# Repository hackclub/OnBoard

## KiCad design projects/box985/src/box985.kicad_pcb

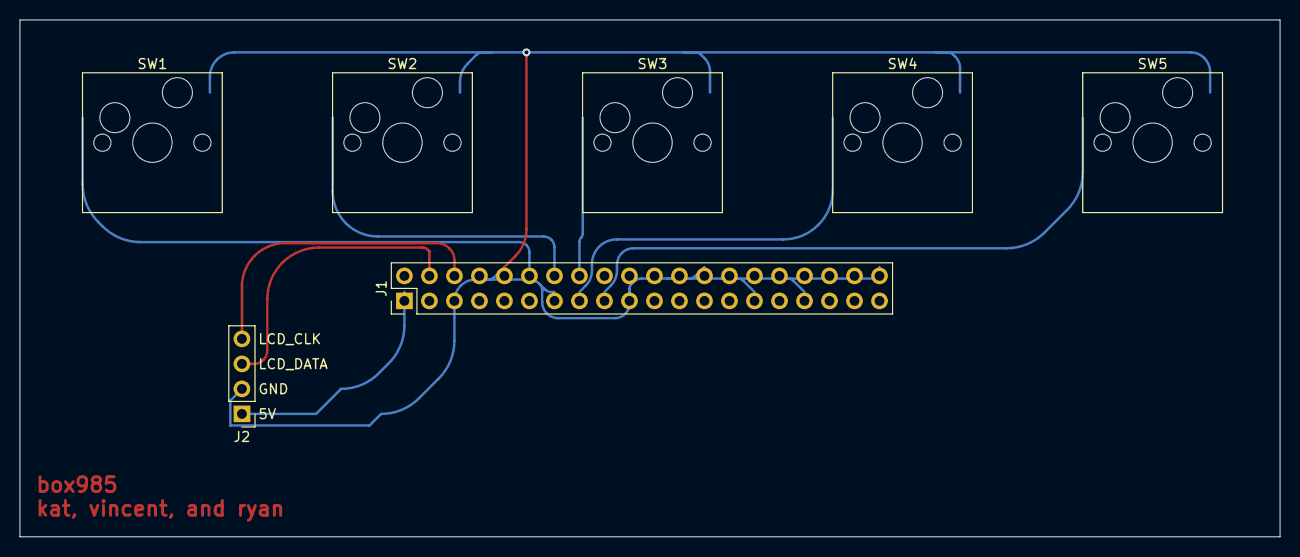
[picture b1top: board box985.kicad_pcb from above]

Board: 2 copper layers, 128.0 x 52.5 mm, 7 parts (0 on the bottom side), 9 nets.

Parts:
J1: Conn_02x20_Odd_Even; PinHeader_2x20_P2.54mm_Vertical
J2: Conn_01x04; PinHeader_1x04_P2.54mm_Vertical
SW1, SW2, SW3, SW4, SW5: Switch; Hotswap_MX

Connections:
+5V: J1.2, J2.1
GND: J1.6, J1.9, J1.14, J1.20, J1.25, J1.30, J1.34, J1.39, J2.2, SW1.2, SW2.2, SW3.2, SW4.2, SW5.2
GPIO 17: J1.11, SW1.1
GPIO 22: J1.15, SW3.1
GPIO 23: J1.16, SW4.1
GPIO 24: J1.18, SW5.1
GPIO 27: J1.13, SW2.1
LCD_CLK: J1.5, J2.4
LCD_DATA: J1.3, J2.3

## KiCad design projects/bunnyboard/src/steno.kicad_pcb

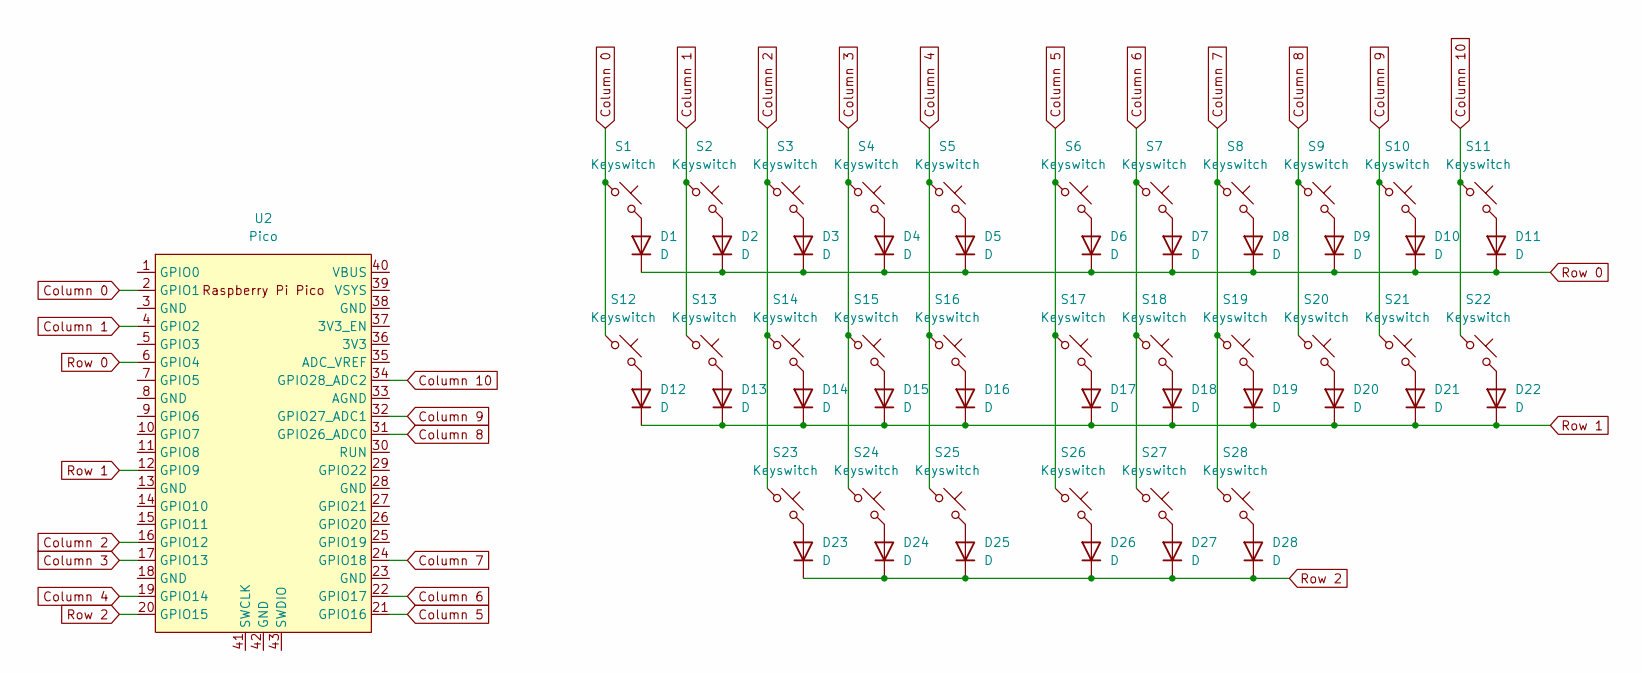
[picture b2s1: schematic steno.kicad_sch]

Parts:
D1, D2, D3, D4, D5, D6, D7, D8, D9, D10, D11, D12, D13, D14, D15, D16, D17, D18, D19, D20, D21, D22, D23, D24, D25, D26, D27, D28: D; Diode_DO-35
S1, S2, S3, S4, S5, S6, S7, S8, S9, S10, S11, S12, S13, S14, S15, S16, S17, S18, S19, S20, S21, S22, S23, S24, S25, S26, S27, S28: Keyswitch; Choc_V1_1.00u
U2: Pico; RPi_PicoW_SMD_TH

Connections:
Column 0: S1.1, S12.1, U2.2 (GPIO1)
Column 1: S2.1, S13.1, U2.4 (GPIO2)
Column 2: S3.1, S14.1, S23.1, U2.16 (GPIO12)
Column 3: S4.1, S15.1, S24.1, U2.17 (GPIO13)
Column 4: S5.1, S16.1, S25.1, U2.19 (GPIO14)
Column 5: S6.1, S17.1, S26.1, U2.21 (GPIO16)
Column 6: S7.1, S18.1, S27.1, U2.22 (GPIO17)
Column 7: S8.1, S19.1, S28.1, U2.24 (GPIO18)
Column 8: S9.1, S20.1, U2.31 (GPIO26_ADC0)
Column 9: S10.1, S21.1, U2.32 (GPIO27_ADC1)
Column 10: S11.1, S22.1, U2.34 (GPIO28_ADC2)
unnamed: D1.2 (A), S1.2
unnamed: D2.2 (A), S2.2
unnamed: D3.2 (A), S3.2
unnamed: D4.2 (A), S4.2
unnamed: D5.2 (A), S5.2
unnamed: D6.2 (A), S6.2
unnamed: D7.2 (A), S7.2
unnamed: D8.2 (A), S8.2
unnamed: D9.2 (A), S9.2
unnamed: D10.2 (A), S10.2
unnamed: D11.2 (A), S11.2
unnamed: D12.2 (A), S12.2
unnamed: D13.2 (A), S13.2
unnamed: D14.2 (A), S14.2
unnamed: D15.2 (A), S15.2
unnamed: D16.2 (A), S16.2
unnamed: D17.2 (A), S17.2
unnamed: D18.2 (A), S18.2
unnamed: D19.2 (A), S19.2
unnamed: D20.2 (A), S20.2
unnamed: D21.2 (A), S21.2
unnamed: D22.2 (A), S22.2
unnamed: D23.2 (A), S23.2
unnamed: D24.2 (A), S24.2
unnamed: D25.2 (A), S25.2
unnamed: D26.2 (A), S26.2
unnamed: D27.2 (A), S27.2
unnamed: D28.2 (A), S28.2
Row 0: D1.1 (K), D2.1 (K), D3.1 (K), D4.1 (K), D5.1 (K), D6.1 (K), D7.1 (K), D8.1 (K), D9.1 (K), D10.1 (K), D11.1 (K), U2.6 (GPIO4)
Row 1: D12.1 (K), D13.1 (K), D14.1 (K), D15.1 (K), D16.1 (K), D17.1 (K), D18.1 (K), D19.1 (K), D20.1 (K), D21.1 (K), D22.1 (K), U2.12 (GPIO9)
Row 2: D23.1 (K), D24.1 (K), D25.1 (K), D26.1 (K), D27.1 (K), D28.1 (K), U2.20 (GPIO15)

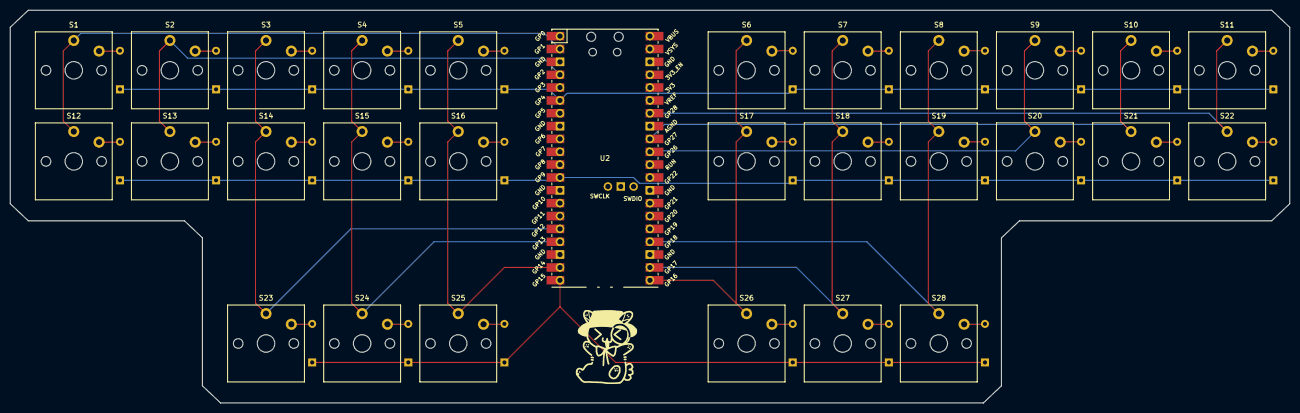
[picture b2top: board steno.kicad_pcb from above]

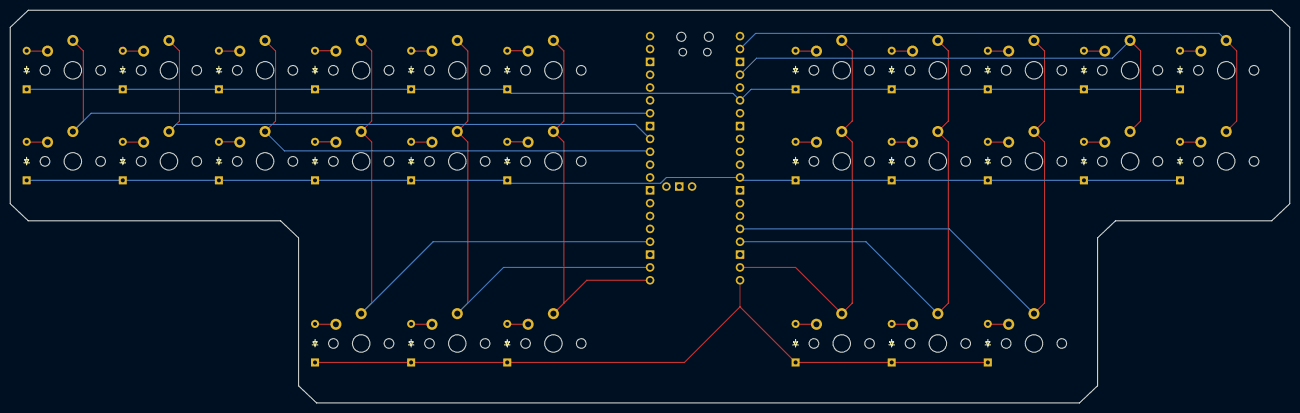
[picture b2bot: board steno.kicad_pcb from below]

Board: 2 copper layers, 252.9 x 77.6 mm, 57 parts (28 on the bottom side), 42 nets.

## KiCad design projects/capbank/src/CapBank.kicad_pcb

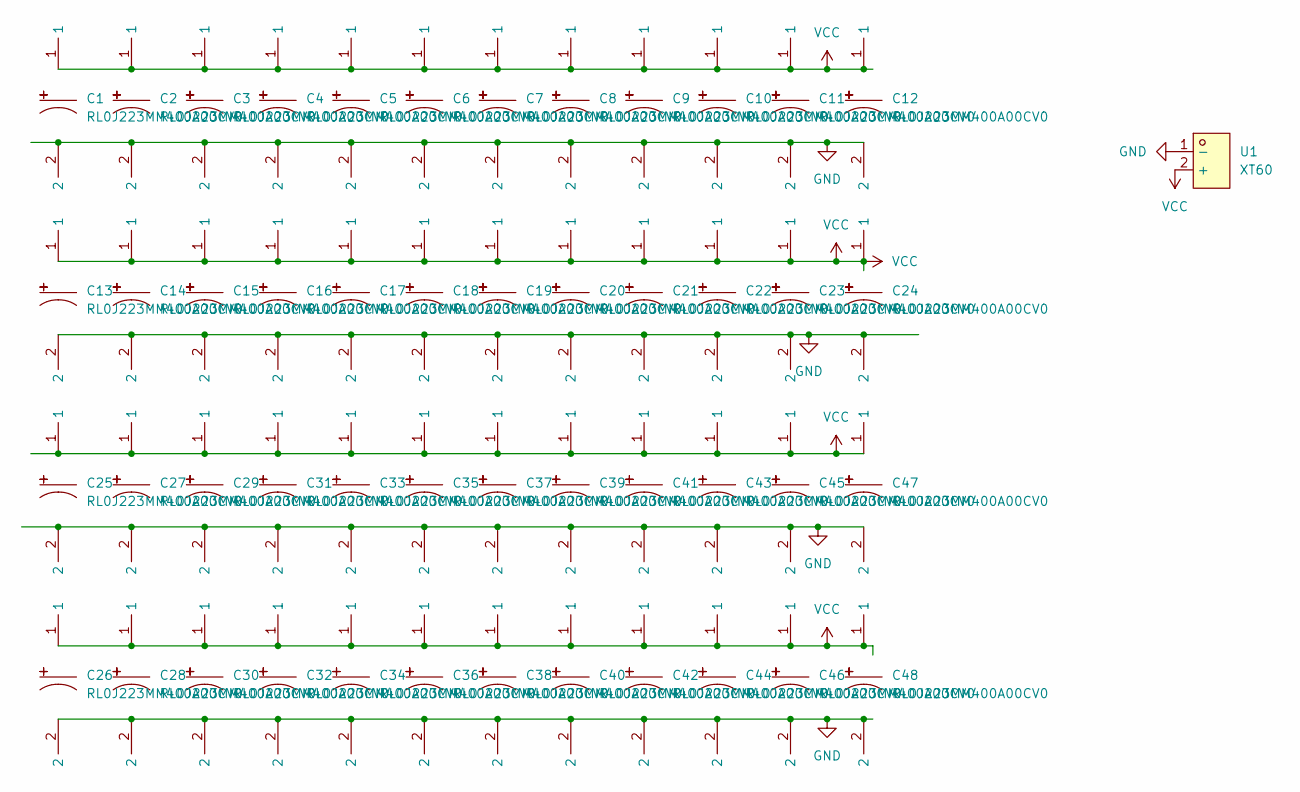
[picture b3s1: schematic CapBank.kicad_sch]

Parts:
C1, C2, C3, C4, C5, C6, C7, C8, C9, C10, C11, C12, C13, C14, C15, C16, C17, C18, C19, C20, C21, C22, C23, C24, C25, C26, C27, C28, C29, C30, C31, C32, C33, C34, C35, C36, C37, C38, C39, C40, C41, C42, C43, C44, C45, C46, C47, C48: RL0J223MM400A00CV0; CAP-TH_BD18.0-P7.50-D1.2-FD; LCSC Part C315548
U1: XT60; CONN-TH_XT60; LCSC Part C98733

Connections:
GND: C1.2, C2.2, C3.2, C4.2, C5.2, C6.2, C7.2, C8.2, C9.2, C10.2, C11.2, C12.2, C13.2, C14.2, C15.2, C16.2, C17.2, C18.2, C19.2, C20.2, C21.2, C22.2, C23.2, C24.2, C25.2, C26.2, C27.2, C28.2, C29.2, C30.2, C31.2, C32.2, C33.2, C34.2, C35.2, C36.2, C37.2, C38.2, C39.2, C40.2, C41.2, C42.2, C43.2, C44.2, C45.2, C46.2, C47.2, C48.2, U1.1 (-)
VCC: C1.1, C2.1, C3.1, C4.1, C5.1, C6.1, C7.1, C8.1, C9.1, C10.1, C11.1, C12.1, C13.1, C14.1, C15.1, C16.1, C17.1, C18.1, C19.1, C20.1, C21.1, C22.1, C23.1, C24.1, C25.1, C26.1, C27.1, C28.1, C29.1, C30.1, C31.1, C32.1, C33.1, C34.1, C35.1, C36.1, C37.1, C38.1, C39.1, C40.1, C41.1, C42.1, C43.1, C44.1, C45.1, C46.1, C47.1, C48.1, U1.2 (+)

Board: 2 copper layers, 49 parts (0 on the bottom side), 2 nets, no tracks yet.

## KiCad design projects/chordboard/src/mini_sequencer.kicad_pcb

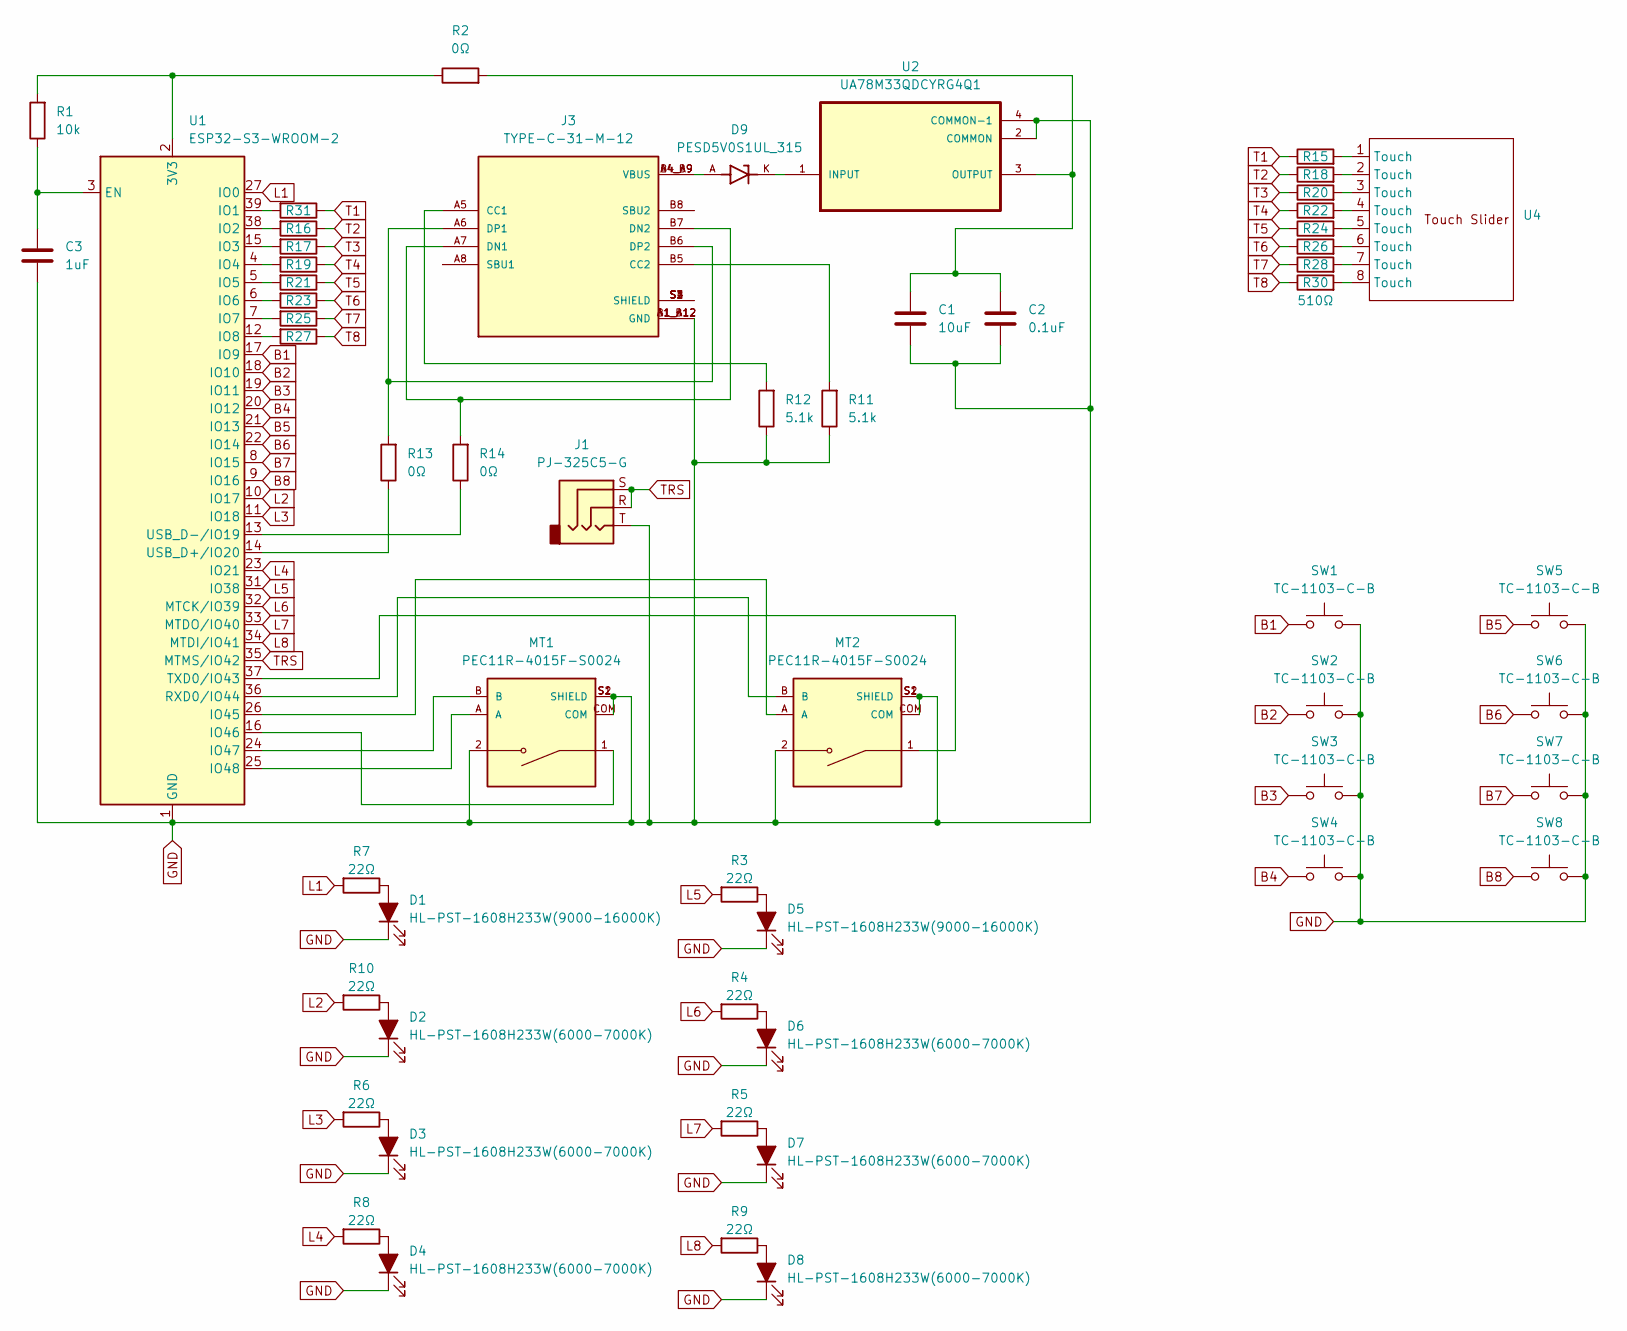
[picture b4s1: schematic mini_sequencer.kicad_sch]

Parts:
C1: 10uF; C1608X5R1E106M080AC_CAPC1608X100N; LCSC C2909630
C2: 0.1uF; CGA3E2X7R1H104K080AA_CAPC1608X90N; LCSC C149620
C3: 1uF; EMK107B7105KA-T_CAPC1608X90N; LCSC C385893
D1, D5: HL-PST-1608H233W(9000-16000K); LED_0603_1608Metric; LCSC C219226
D2, D3, D4, D6, D7, D8: HL-PST-1608H233W(6000-7000K); LED_0603_1608Metric; LCSC C219227
D9: PESD5V0S1UL_315; PESD5V0S1UL_315_DIO_PESD5V0S1UL_315; LCSC C85402
J1: PJ-325C5-G; Jack_3.5mm_CUI_SJ1-3535NG_Horizontal; LCSC C692438
J3: TYPE-C-31-M-12; TYPE-C-31-M-12_HRO_TYPE-C-31-M-12; PARTREV 2020.12.08; LCSC C165948
MT1, MT2: PEC11R-4015F-S0024; PEC11R-4215F-S0024_XDCR_PEC11R-4215F-S0024; PARTREV Rev. 09/19; LCSC C143789
R1: 10k; MCS04020C1002FE000_RESC1005X37N; LCSC C190095
R2, R13, R14, R16, R17, R19, R21, R23, R25, R27, R31: 0Ω; R_0201_0603Metric; LCSC C4085635
R3, R4, R5, R6, R7, R8, R9, R10: 22Ω; R_0201_0603Metric; LCSC C862626
R11, R12: 5.1k; R_0201_0603Metric; LCSC C122969
R15, R18, R20, R22, R28, R30: 510Ω; R_0201_0603Metric; LCSC C860427
R24, R26: 510Ω; R_0201_0603Metric
SW1, SW2, SW3, SW4, SW5, SW6, SW7, SW8: TC-1103-C-B; SW_PUSH-12mm; LCSC C840834
U1: ESP32-S3-WROOM-2; LCSC C2913202
U2: UA78M33QDCYRG4Q1; UA78M33QDCYRG4Q1_SOT230P700X180-4N; LCSC C131952
U4: TouchSlider-8_50x15mm

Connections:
B1: SW1.1, U1.17 (IO9)
B2: SW2.1, U1.18 (IO10)
B3: SW3.1, U1.19 (IO11)
B4: SW4.1, U1.20 (IO12)
B5: SW5.1, U1.21 (IO13)
B6: SW6.1, U1.22 (IO14)
B7: SW7.1, U1.8 (IO15)
B8: SW8.1, U1.9 (IO16)
GND: C1.2, C2.2, C3.1, D1.1 (K), D2.1 (K), D3.1 (K), D4.1 (K), D5.1 (K), D6.1 (K), D7.1 (K), D8.1 (K), J1.T, J3.A1_B12 (GND), J3.B1_A12 (GND), MT1.2, MT1.COM, MT1.S1 (SHIELD), MT1.S2 (SHIELD), MT2.2, MT2.COM, MT2.S1 (SHIELD), MT2.S2 (SHIELD), R11.1, R12.1, SW1.2, SW2.2, SW3.2, SW4.2, SW5.2, SW6.2, SW7.2, SW8.2, U1.1 (GND), U1.40 (GND), U1.41 (GND), U2.2 (COMMON), U2.4 (COMMON-1)
L1: R7.2, U1.27 (IO0)
L2: R10.2, U1.10 (IO17)
L3: R6.2, U1.11 (IO18)
L4: R8.2, U1.23 (IO21)
L5: R3.2, U1.31 (IO38)
L6: R4.2, U1.32 (MTCK/IO39)
L7: R5.2, U1.33 (MTDO/IO40)
L8: R9.2, U1.34 (MTDI/IO41)
unnamed: D1.2 (A), R7.1
unnamed: D2.2 (A), R10.1
unnamed: D3.2 (A), R6.1
unnamed: D4.2 (A), R8.1
unnamed: D5.2 (A), R3.1
unnamed: D6.2 (A), R4.1
unnamed: D7.2 (A), R5.1
unnamed: D8.2 (A), R9.1
unnamed: D9.A, J3.A4_B9 (VBUS), J3.B4_A9 (VBUS)
unnamed: J3.A5 (CC1), R12.2
unnamed: J3.B5 (CC2), R11.2
unnamed: J3.A7 (DN1), J3.B7 (DN2), R14.2
unnamed: J3.A6 (DP1), J3.B6 (DP2), R13.2
unnamed: J3.S1 (SHIELD), J3.S2 (SHIELD), J3.S3 (SHIELD), J3.S4 (SHIELD)
unnamed: R15.2, U4.1 (Touch)
unnamed: R18.2, U4.2 (Touch)
unnamed: R20.2, U4.3 (Touch)
unnamed: R22.2, U4.4 (Touch)
unnamed: R24.2, U4.5 (Touch)
unnamed: R26.2, U4.6 (Touch)
unnamed: R28.2, U4.7 (Touch)
unnamed: R30.2, U4.8 (Touch)
unnamed: R1.2, R2.1, U1.2 (3V3)
unnamed: C3.2, R1.1, U1.3 (EN)
unnamed: R31.2, U1.39 (IO1)
unnamed: R16.2, U1.38 (IO2)
unnamed: R17.2, U1.15 (IO3)
unnamed: R19.2, U1.4 (IO4)
unnamed: R21.2, U1.5 (IO5)
unnamed: R23.2, U1.6 (IO6)
unnamed: R25.2, U1.7 (IO7)
unnamed: R27.2, U1.12 (IO8)
unnamed: MT2.A, U1.26 (IO45)
unnamed: MT1.1, U1.16 (IO46)
unnamed: MT1.B, U1.24 (IO47)
unnamed: MT1.A, U1.25 (IO48)
unnamed: MT2.B, U1.36 (RXD0/IO44)
unnamed: MT2.1, U1.37 (TXD0/IO43)
unnamed: R13.1, U1.14 (USB_D+/IO20)
unnamed: R14.1, U1.13 (USB_D-/IO19)
unnamed: D9.K, U2.1 (INPUT)
unnamed: C1.1, C2.1, R2.2, U2.3 (OUTPUT)
T1: R15.1, R31.1
T2: R16.1, R18.1
T3: R17.1, R20.1
T4: R19.1, R22.1
T5: R21.1, R24.1
T6: R23.1, R26.1
T7: R25.1, R28.1
T8: R27.1, R30.1
TRS: J1.R, J1.S, U1.35 (MTMS/IO42)

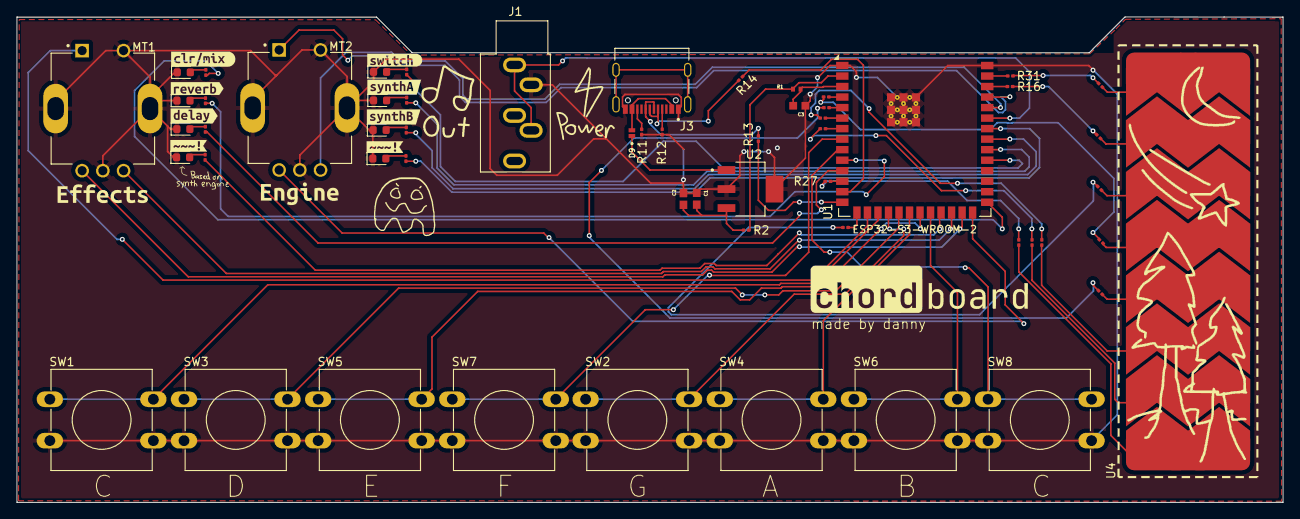
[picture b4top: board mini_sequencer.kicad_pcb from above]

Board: 2 copper layers, 152.9 x 58.6 mm, 67 parts (0 on the bottom side), 68 nets.

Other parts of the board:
kibuzzard-66F9FCB2: G***; kibuzzard-66F9FCB2
kibuzzard-66F9FCDF: G***; kibuzzard-66F9FCDF
kibuzzard-66F9FCF2: G***; kibuzzard-66F9FCF2
kibuzzard-66F9FCF7: G***; kibuzzard-66F9FCF7
kibuzzard-66F9FD07: G***; kibuzzard-66F9FD07
kibuzzard-66F9FD26: G***; kibuzzard-66F9FD26
kibuzzard-66F9FD78: G***; kibuzzard-66F9FD78
kibuzzard-66FCC2B4: G***; kibuzzard-66FCC2B4
kibuzzard-66FCC410: G***; kibuzzard-66FCC410
kibuzzard-6702CE24: G***; kibuzzard-6702CE24

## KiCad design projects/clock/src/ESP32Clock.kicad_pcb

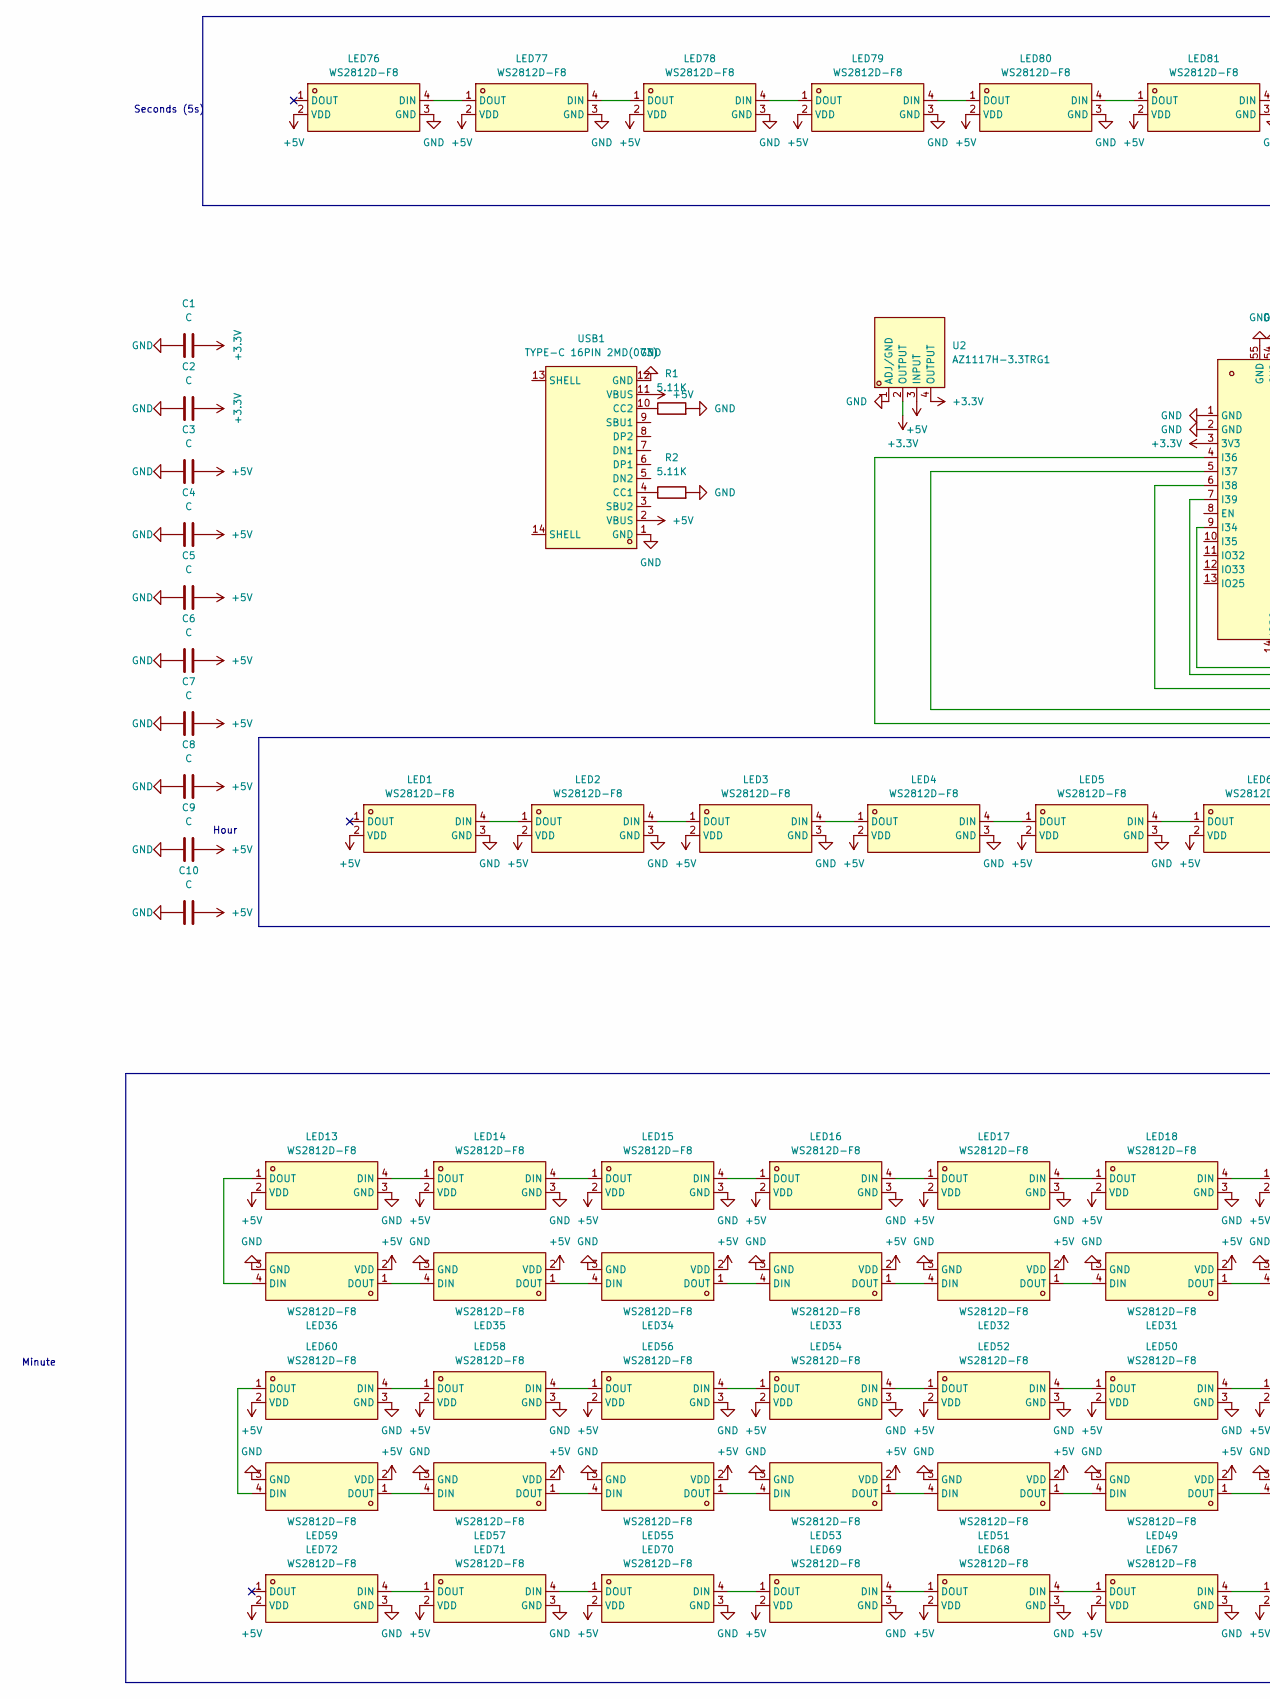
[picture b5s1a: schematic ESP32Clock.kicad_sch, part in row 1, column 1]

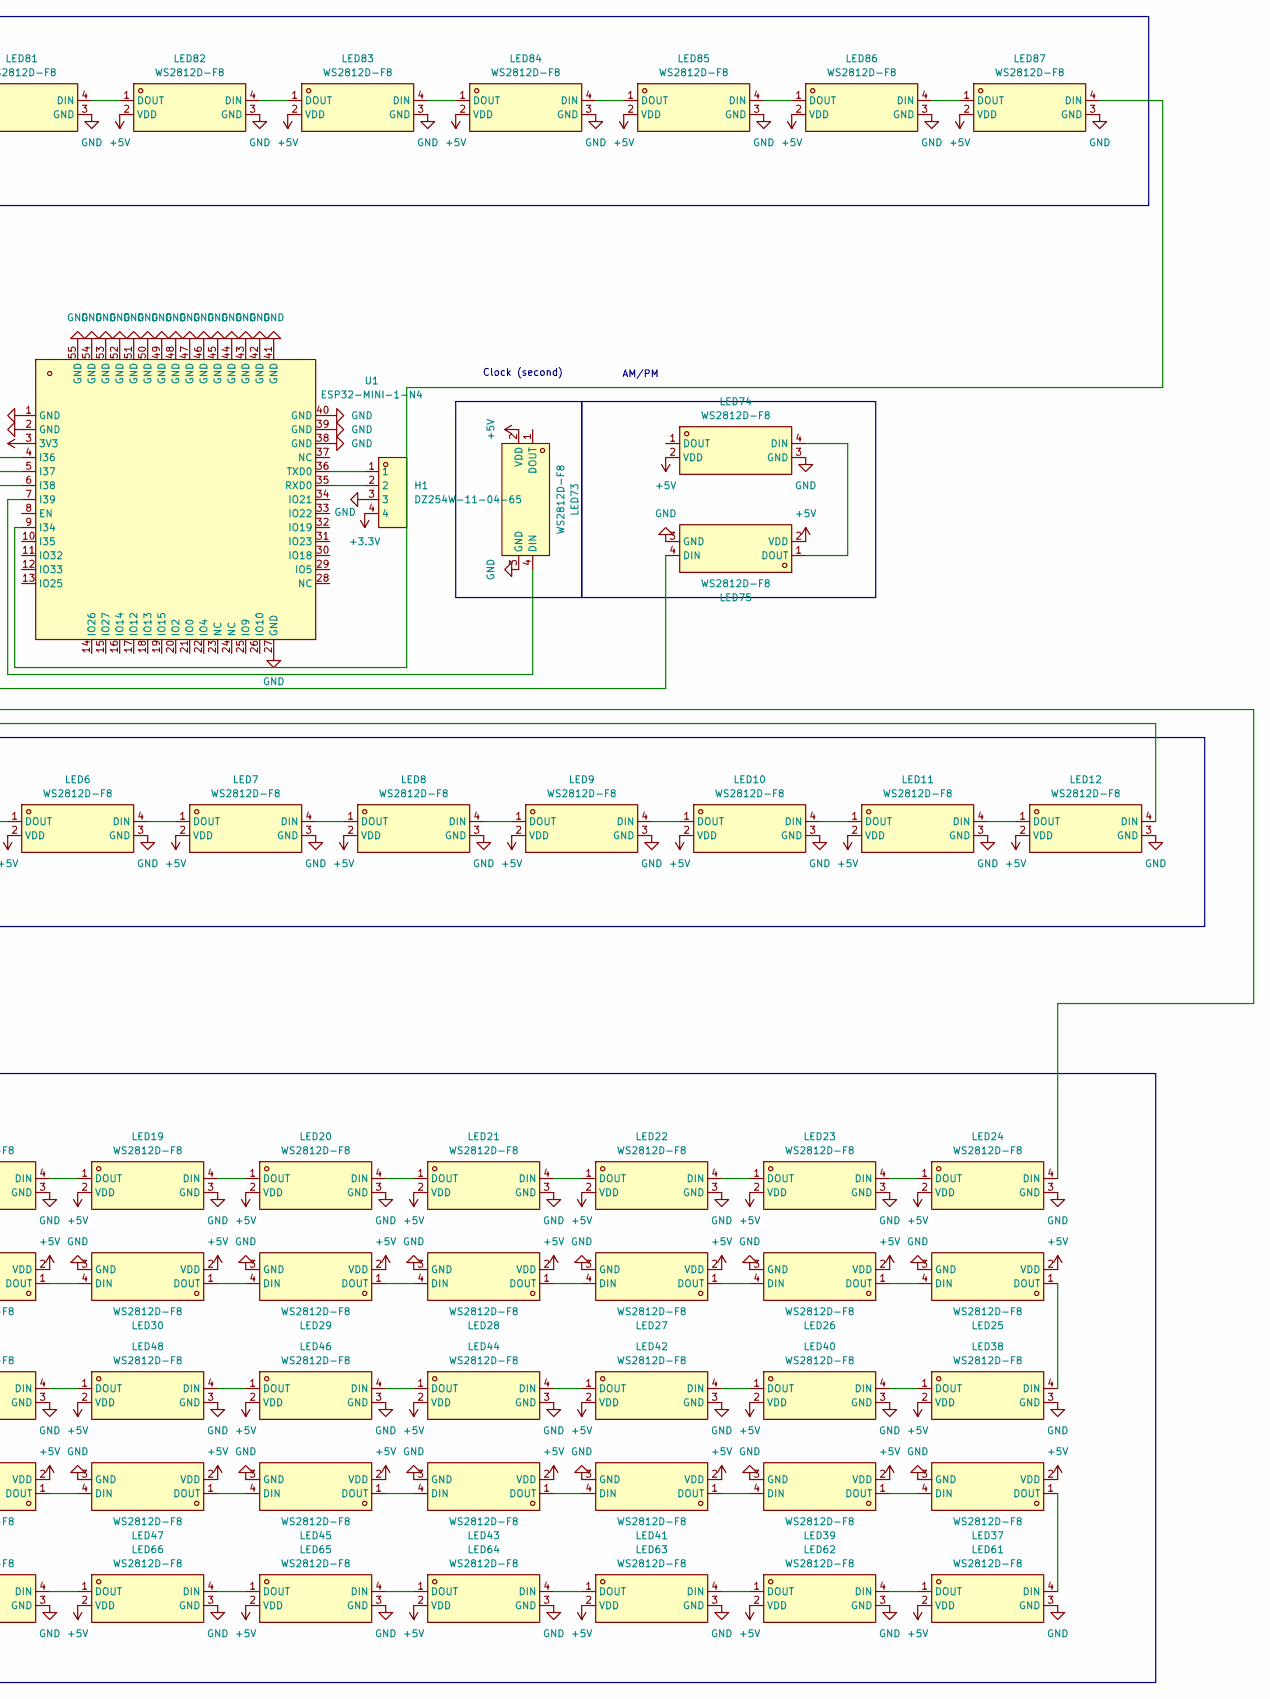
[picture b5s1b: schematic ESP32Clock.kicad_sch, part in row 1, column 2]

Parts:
C1, C2, C3, C4, C5, C6, C7, C8, C9, C10: C; C_0603_1608Metric; LCSC C19702
H1: DZ254W-11-04-65; HDR-TH_4P-P2.54-H-M-W10.3; LCSC Part C2935929
LED1, LED2, LED3, LED4, LED5, LED6, LED7, LED8, LED9, LED10, LED11, LED12, LED13, LED14, LED15, LED16, LED17, LED18, LED19, LED20, LED21, LED22, LED23, LED24, LED25, LED26, LED27, LED28, LED29, LED30, LED31, LED32, LED33, LED34, LED35, LED36, LED37, LED38, LED39, LED40, LED41, LED42, LED43, LED44, LED45, LED46, LED47, LED48, LED49, LED50, LED51, LED52, LED53, LED54, LED55, LED56, LED57, LED58, LED59, LED60, LED61, LED62, LED63, LED64, LED65, LED66, LED67, LED68, LED69, LED70, LED71, LED72, LED73, LED74, LED75, LED76, LED77, LED78, LED79, LED80, LED81, LED82, LED83, LED84, LED85, LED86, LED87: WS2812D-F8; LED-TH_WS2812D-F8; LCSC Part C139126
R1, R2: 5.11K; R_0603_1608Metric; LCSC C112314
U1: ESP32-MINI-1-N4; WIFI-SMD_ESP32-MINI-1; LCSC Part C2980305
U2: AZ1117H-3.3TRG1; SOT-223-3_L6.5-W3.4-P2.30-LS7.0-BR; LCSC Part C110474
USB1: TYPE-C 16PIN 2MD(073); USB-C-SMD_TYPE-C-6PIN-2MD-073; LCSC Part C2765186

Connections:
+3.3V: C1.2, C2.2, H1.4, U1.3 (3V3), U2.2 (OUTPUT), U2.4 (OUTPUT)
+5V: C3.2, C4.2, C5.2, C6.2, C7.2, C8.2, C9.2, C10.2, LED1.2 (VDD), LED2.2 (VDD), LED3.2 (VDD), LED4.2 (VDD), LED5.2 (VDD), LED6.2 (VDD), LED7.2 (VDD), LED8.2 (VDD), LED9.2 (VDD), LED10.2 (VDD), LED11.2 (VDD), LED12.2 (VDD), LED13.2 (VDD), LED14.2 (VDD), LED15.2 (VDD), LED16.2 (VDD), LED17.2 (VDD), LED18.2 (VDD), LED19.2 (VDD), LED20.2 (VDD), LED21.2 (VDD), LED22.2 (VDD), LED23.2 (VDD), LED24.2 (VDD), LED25.2 (VDD), LED26.2 (VDD), LED27.2 (VDD), LED28.2 (VDD), LED29.2 (VDD), LED30.2 (VDD), LED31.2 (VDD), LED32.2 (VDD), LED33.2 (VDD), LED34.2 (VDD), LED35.2 (VDD), LED36.2 (VDD), LED37.2 (VDD), LED38.2 (VDD), LED39.2 (VDD), LED40.2 (VDD), LED41.2 (VDD), LED42.2 (VDD), LED43.2 (VDD), LED44.2 (VDD), LED45.2 (VDD), LED46.2 (VDD), LED47.2 (VDD), LED48.2 (VDD), LED49.2 (VDD), LED50.2 (VDD), LED51.2 (VDD), LED52.2 (VDD), LED53.2 (VDD), LED54.2 (VDD), LED55.2 (VDD), LED56.2 (VDD), LED57.2 (VDD), LED58.2 (VDD), LED59.2 (VDD), LED60.2 (VDD), LED61.2 (VDD), LED62.2 (VDD), LED63.2 (VDD), LED64.2 (VDD), LED65.2 (VDD), LED66.2 (VDD), LED67.2 (VDD), LED68.2 (VDD), LED69.2 (VDD), LED70.2 (VDD), LED71.2 (VDD), LED72.2 (VDD), LED73.2 (VDD), LED74.2 (VDD), LED75.2 (VDD), LED76.2 (VDD), LED77.2 (VDD), LED78.2 (VDD), LED79.2 (VDD), LED80.2 (VDD), LED81.2 (VDD), LED82.2 (VDD), LED83.2 (VDD), LED84.2 (VDD), LED85.2 (VDD), LED86.2 (VDD), LED87.2 (VDD), U2.3 (INPUT), USB1.2 (VBUS), USB1.11 (VBUS)
GND: C1.1, C2.1, C3.1, C4.1, C5.1, C6.1, C7.1, C8.1, C9.1, C10.1, H1.3, LED1.3 (GND), LED2.3 (GND), LED3.3 (GND), LED4.3 (GND), LED5.3 (GND), LED6.3 (GND), LED7.3 (GND), LED8.3 (GND), LED9.3 (GND), LED10.3 (GND), LED11.3 (GND), LED12.3 (GND), LED13.3 (GND), LED14.3 (GND), LED15.3 (GND), LED16.3 (GND), LED17.3 (GND), LED18.3 (GND), LED19.3 (GND), LED20.3 (GND), LED21.3 (GND), LED22.3 (GND), LED23.3 (GND), LED24.3 (GND), LED25.3 (GND), LED26.3 (GND), LED27.3 (GND), LED28.3 (GND), LED29.3 (GND), LED30.3 (GND), LED31.3 (GND), LED32.3 (GND), LED33.3 (GND), LED34.3 (GND), LED35.3 (GND), LED36.3 (GND), LED37.3 (GND), LED38.3 (GND), LED39.3 (GND), LED40.3 (GND), LED41.3 (GND), LED42.3 (GND), LED43.3 (GND), LED44.3 (GND), LED45.3 (GND), LED46.3 (GND), LED47.3 (GND), LED48.3 (GND), LED49.3 (GND), LED50.3 (GND), LED51.3 (GND), LED52.3 (GND), LED53.3 (GND), LED54.3 (GND), LED55.3 (GND), LED56.3 (GND), LED57.3 (GND), LED58.3 (GND), LED59.3 (GND), LED60.3 (GND), LED61.3 (GND), LED62.3 (GND), LED63.3 (GND), LED64.3 (GND), LED65.3 (GND), LED66.3 (GND), LED67.3 (GND), LED68.3 (GND), LED69.3 (GND), LED70.3 (GND), LED71.3 (GND), LED72.3 (GND), LED73.3 (GND), LED74.3 (GND), LED75.3 (GND), LED76.3 (GND), LED77.3 (GND), LED78.3 (GND), LED79.3 (GND), LED80.3 (GND), LED81.3 (GND), LED82.3 (GND), LED83.3 (GND), LED84.3 (GND), LED85.3 (GND), LED86.3 (GND), LED87.3 (GND), R1.2, R2.2, U1.1 (GND), U1.2 (GND), U1.27 (GND), U1.38 (GND), U1.39 (GND), U1.40 (GND), U1.41 (GND), U1.42 (GND), U1.43 (GND), U1.44 (GND), U1.45 (GND), U1.46 (GND), U1.47 (GND), U1.48 (GND), U1.49 (GND), U1.50 (GND), U1.51 (GND), U1.52 (GND), U1.53 (GND), U1.54 (GND), U1.55 (GND), U2.1 (ADJ/GND), USB1.1 (GND), USB1.12 (GND)
unnamed: LED1.4 (DIN), LED2.1 (DOUT)
unnamed: LED2.4 (DIN), LED3.1 (DOUT)
unnamed: LED3.4 (DIN), LED4.1 (DOUT)
unnamed: LED4.4 (DIN), LED5.1 (DOUT)
unnamed: LED5.4 (DIN), LED6.1 (DOUT)
unnamed: LED6.4 (DIN), LED7.1 (DOUT)
unnamed: LED7.4 (DIN), LED8.1 (DOUT)
unnamed: LED8.4 (DIN), LED9.1 (DOUT)
unnamed: LED10.4 (DIN), LED11.1 (DOUT)
unnamed: LED9.4 (DIN), LED10.1 (DOUT)
unnamed: LED11.4 (DIN), LED12.1 (DOUT)
unnamed: LED12.4 (DIN), U1.4 (I36)
unnamed: LED13.4 (DIN), LED14.1 (DOUT)
unnamed: LED13.1 (DOUT), LED36.4 (DIN)
unnamed: LED14.4 (DIN), LED15.1 (DOUT)
unnamed: LED15.4 (DIN), LED16.1 (DOUT)
unnamed: LED16.4 (DIN), LED17.1 (DOUT)
unnamed: LED17.4 (DIN), LED18.1 (DOUT)
unnamed: LED18.4 (DIN), LED19.1 (DOUT)
unnamed: LED19.4 (DIN), LED20.1 (DOUT)
unnamed: LED20.4 (DIN), LED21.1 (DOUT)
unnamed: LED21.4 (DIN), LED22.1 (DOUT)
unnamed: LED22.4 (DIN), LED23.1 (DOUT)
unnamed: LED23.4 (DIN), LED24.1 (DOUT)
unnamed: LED24.4 (DIN), U1.5 (I37)
unnamed: LED25.4 (DIN), LED26.1 (DOUT)
unnamed: LED25.1 (DOUT), LED38.4 (DIN)
unnamed: LED26.4 (DIN), LED27.1 (DOUT)
unnamed: LED27.4 (DIN), LED28.1 (DOUT)
unnamed: LED28.4 (DIN), LED29.1 (DOUT)
unnamed: LED29.4 (DIN), LED30.1 (DOUT)
unnamed: LED30.4 (DIN), LED31.1 (DOUT)
unnamed: LED31.4 (DIN), LED32.1 (DOUT)
unnamed: LED32.4 (DIN), LED33.1 (DOUT)
unnamed: LED33.4 (DIN), LED34.1 (DOUT)
unnamed: LED34.4 (DIN), LED35.1 (DOUT)
unnamed: LED35.4 (DIN), LED36.1 (DOUT)
unnamed: LED37.4 (DIN), LED39.1 (DOUT)
unnamed: LED37.1 (DOUT), LED61.4 (DIN)
unnamed: LED38.1 (DOUT), LED40.4 (DIN)
unnamed: LED39.4 (DIN), LED41.1 (DOUT)
unnamed: LED40.1 (DOUT), LED42.4 (DIN)
unnamed: LED41.4 (DIN), LED43.1 (DOUT)
unnamed: LED42.1 (DOUT), LED44.4 (DIN)
unnamed: LED43.4 (DIN), LED45.1 (DOUT)
unnamed: LED44.1 (DOUT), LED46.4 (DIN)
unnamed: LED45.4 (DIN), LED47.1 (DOUT)
unnamed: LED46.1 (DOUT), LED48.4 (DIN)
unnamed: LED47.4 (DIN), LED49.1 (DOUT)
unnamed: LED48.1 (DOUT), LED50.4 (DIN)
unnamed: LED49.4 (DIN), LED51.1 (DOUT)
unnamed: LED50.1 (DOUT), LED52.4 (DIN)
unnamed: LED51.4 (DIN), LED53.1 (DOUT)
unnamed: LED52.1 (DOUT), LED54.4 (DIN)
unnamed: LED53.4 (DIN), LED55.1 (DOUT)
unnamed: LED54.1 (DOUT), LED56.4 (DIN)
unnamed: LED55.4 (DIN), LED57.1 (DOUT)
unnamed: LED56.1 (DOUT), LED58.4 (DIN)
unnamed: LED57.4 (DIN), LED59.1 (DOUT)
unnamed: LED58.1 (DOUT), LED60.4 (DIN)
unnamed: LED59.4 (DIN), LED60.1 (DOUT)
unnamed: LED61.1 (DOUT), LED62.4 (DIN)
unnamed: LED62.1 (DOUT), LED63.4 (DIN)
unnamed: LED63.1 (DOUT), LED64.4 (DIN)
unnamed: LED64.1 (DOUT), LED65.4 (DIN)
unnamed: LED65.1 (DOUT), LED66.4 (DIN)
unnamed: LED66.1 (DOUT), LED67.4 (DIN)
unnamed: LED67.1 (DOUT), LED68.4 (DIN)
unnamed: LED68.1 (DOUT), LED69.4 (DIN)
unnamed: LED69.1 (DOUT), LED70.4 (DIN)
unnamed: LED70.1 (DOUT), LED71.4 (DIN)
unnamed: LED71.1 (DOUT), LED72.4 (DIN)
unnamed: LED73.4 (DIN), U1.7 (I39)
unnamed: LED74.4 (DIN), LED75.1 (DOUT)
unnamed: LED75.4 (DIN), U1.6 (I38)
unnamed: LED76.4 (DIN), LED77.1 (DOUT)
unnamed: LED77.4 (DIN), LED78.1 (DOUT)
unnamed: LED78.4 (DIN), LED79.1 (DOUT)
unnamed: LED79.4 (DIN), LED80.1 (DOUT)
unnamed: LED80.4 (DIN), LED81.1 (DOUT)
unnamed: LED81.4 (DIN), LED82.1 (DOUT)
unnamed: LED82.4 (DIN), LED83.1 (DOUT)
unnamed: LED83.4 (DIN), LED84.1 (DOUT)
unnamed: LED84.4 (DIN), LED85.1 (DOUT)
unnamed: LED85.4 (DIN), LED86.1 (DOUT)
unnamed: LED86.4 (DIN), LED87.1 (DOUT)
unnamed: LED87.4 (DIN), U1.9 (I34)
unnamed: H1.2, U1.35 (RXD0)
unnamed: H1.1, U1.36 (TXD0)
unnamed: R2.1, USB1.4 (CC1)
unnamed: R1.1, USB1.10 (CC2)

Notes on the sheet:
Minute
Clock (second)
Hour
Seconds (5s)
AM/PM

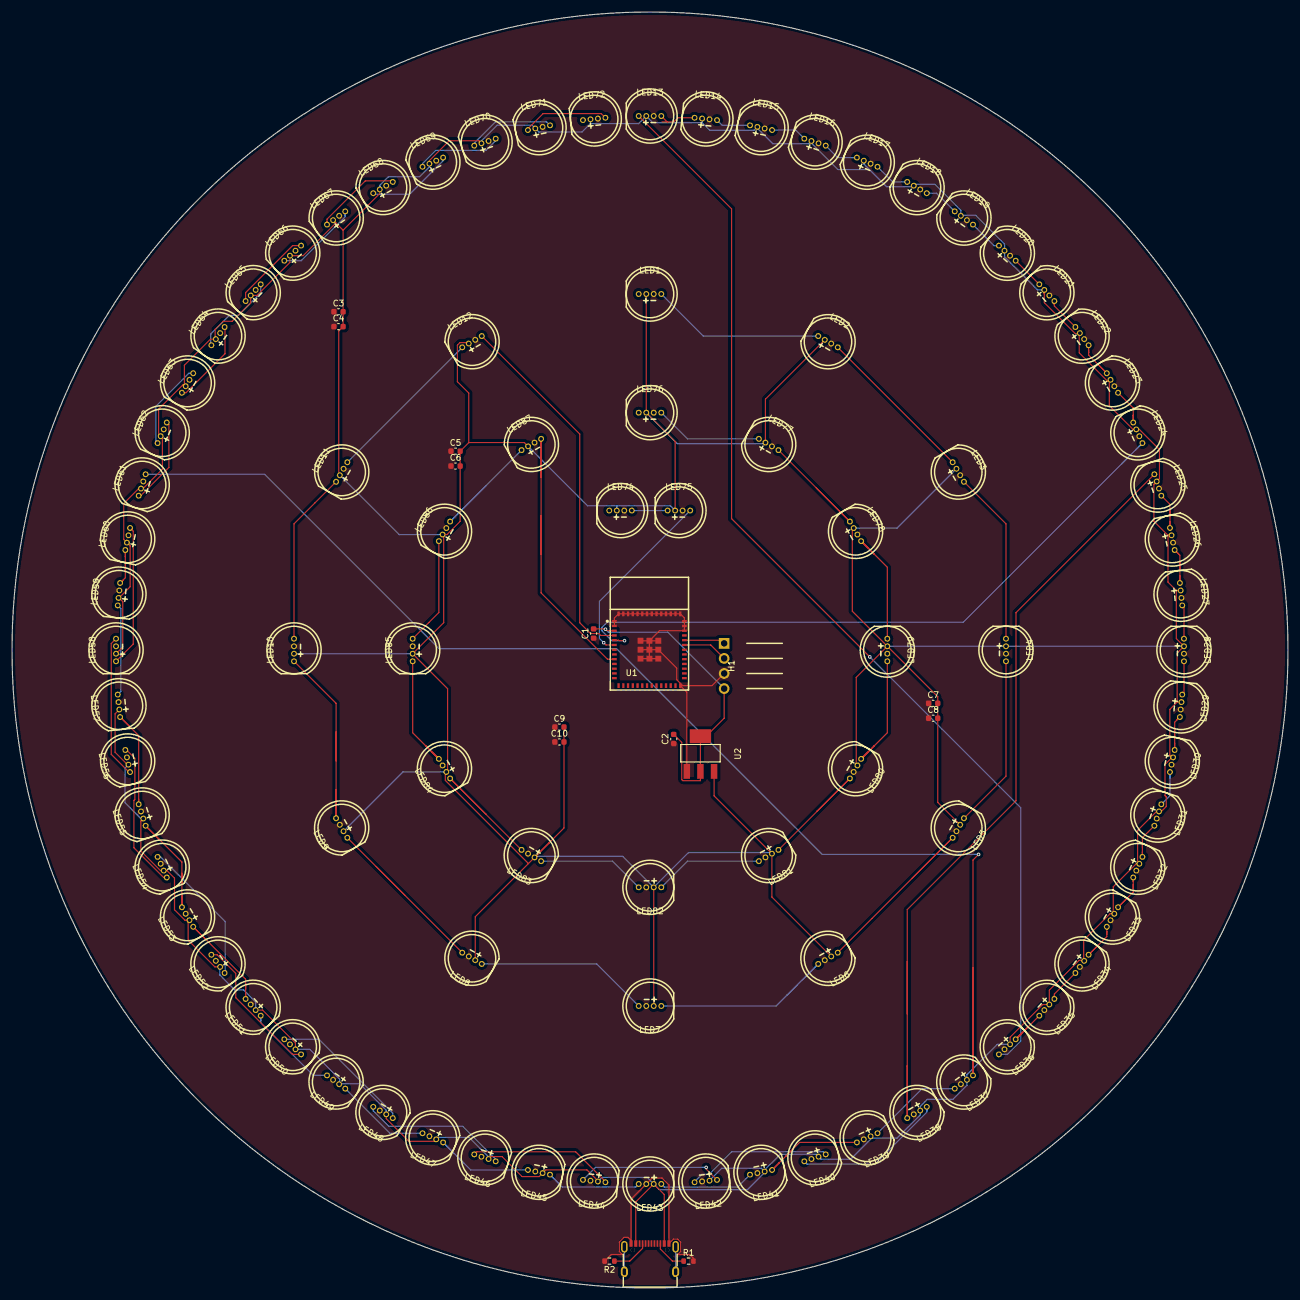
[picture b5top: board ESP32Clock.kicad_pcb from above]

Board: 2 copper layers, 215.1 x 215.1 mm, 102 parts (0 on the bottom side), 93 nets.
